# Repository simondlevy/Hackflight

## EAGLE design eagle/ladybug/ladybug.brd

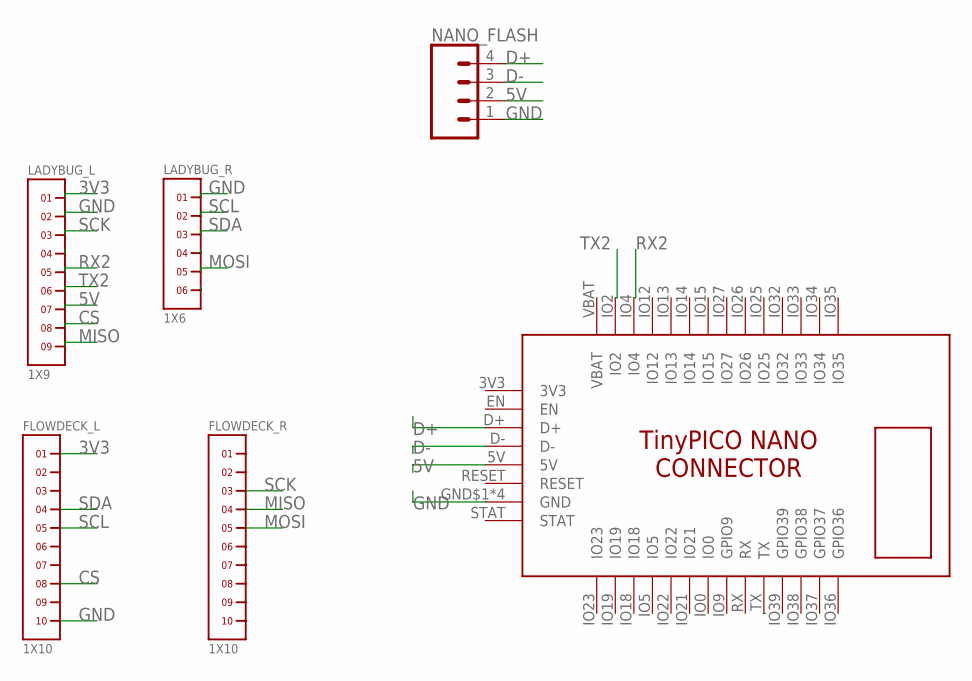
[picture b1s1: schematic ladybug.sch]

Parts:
FLOWDECK_L: 1X10
FLOWDECK_R: 1X10
LADYBUG_L: 1X9
LADYBUG_R: 1X6
NANO_FLASH: CONN_041X04_NO_SILK; 1X04_NO_SILK
U$1: TINYPICO-NANO-CONNECTOR

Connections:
3V3: FLOWDECK_L.1, LADYBUG_L.1, U$1.3V3
5V: LADYBUG_L.7, NANO_FLASH.2, U$1.5V
A0: LADYBUG_R.4
CS: FLOWDECK_L.8, LADYBUG_L.8
D+: NANO_FLASH.4, U$1.D+
D-: NANO_FLASH.3, U$1.D-
GND: FLOWDECK_L.10, LADYBUG_L.2, LADYBUG_R.1, NANO_FLASH.1, U$1.GND$1 (GND), U$1.GND$2 (GND), U$1.GND$3 (GND), U$1.GND$4 (GND)
LED: LADYBUG_L.4
MISO: FLOWDECK_R.4, LADYBUG_L.9
MOSI: FLOWDECK_R.5, LADYBUG_R.5
RX: U$1.TX
RX2: LADYBUG_L.5, U$1.IO4
SCK: FLOWDECK_R.3, LADYBUG_L.3
SCL: FLOWDECK_L.5, LADYBUG_R.2
SDA: FLOWDECK_L.4, LADYBUG_R.3
TX1: LADYBUG_R.6
TX2: LADYBUG_L.6, U$1.IO2
VBAT: U$1.VBAT

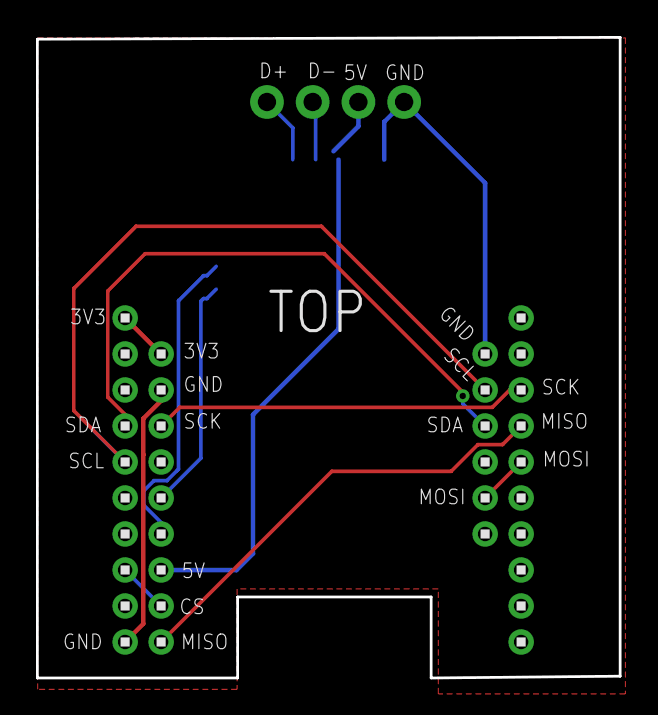
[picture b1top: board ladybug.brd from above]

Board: 2 copper layers, 32.4 x 35.6 mm, 6 parts (1 on the bottom side), 13 nets.

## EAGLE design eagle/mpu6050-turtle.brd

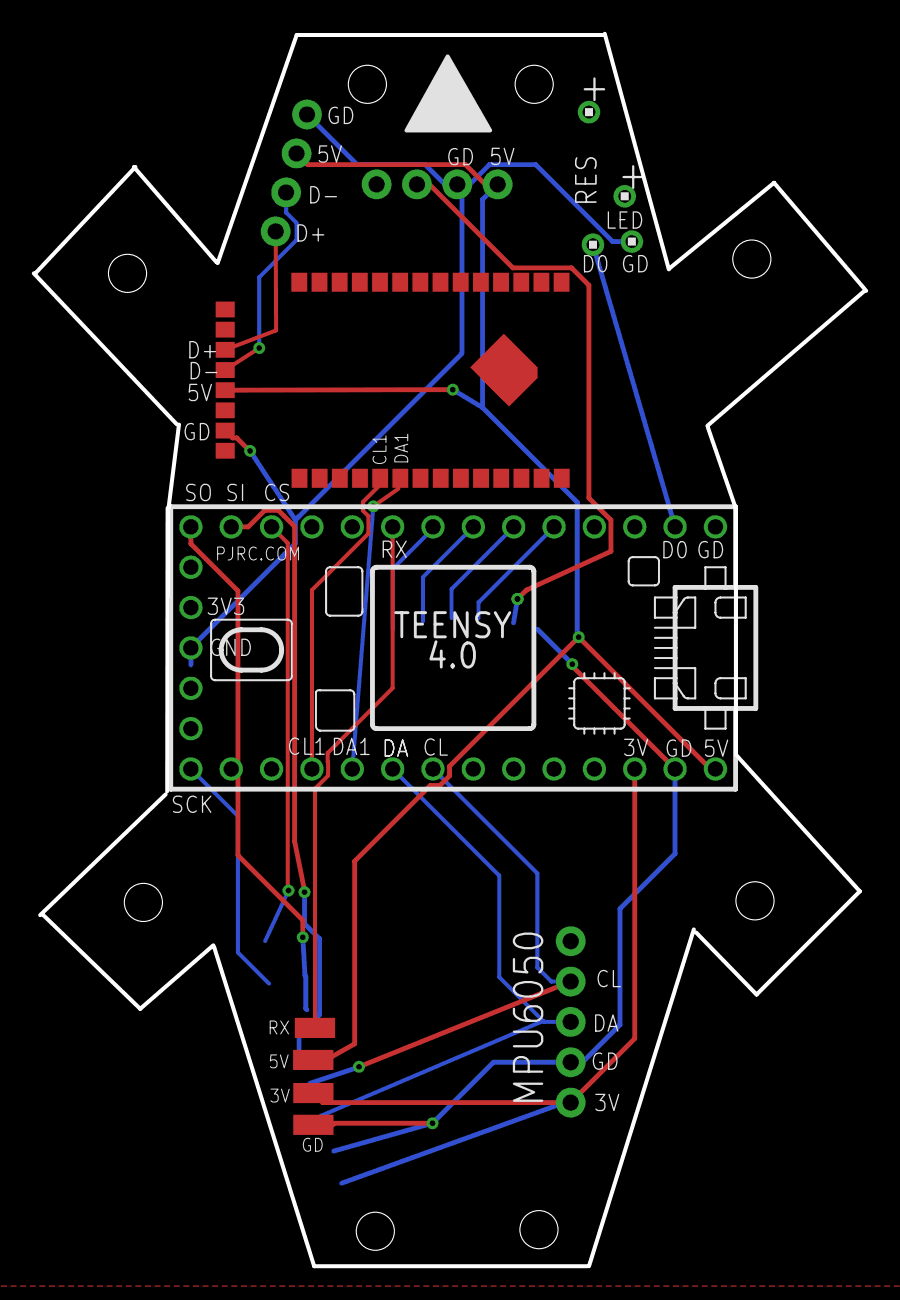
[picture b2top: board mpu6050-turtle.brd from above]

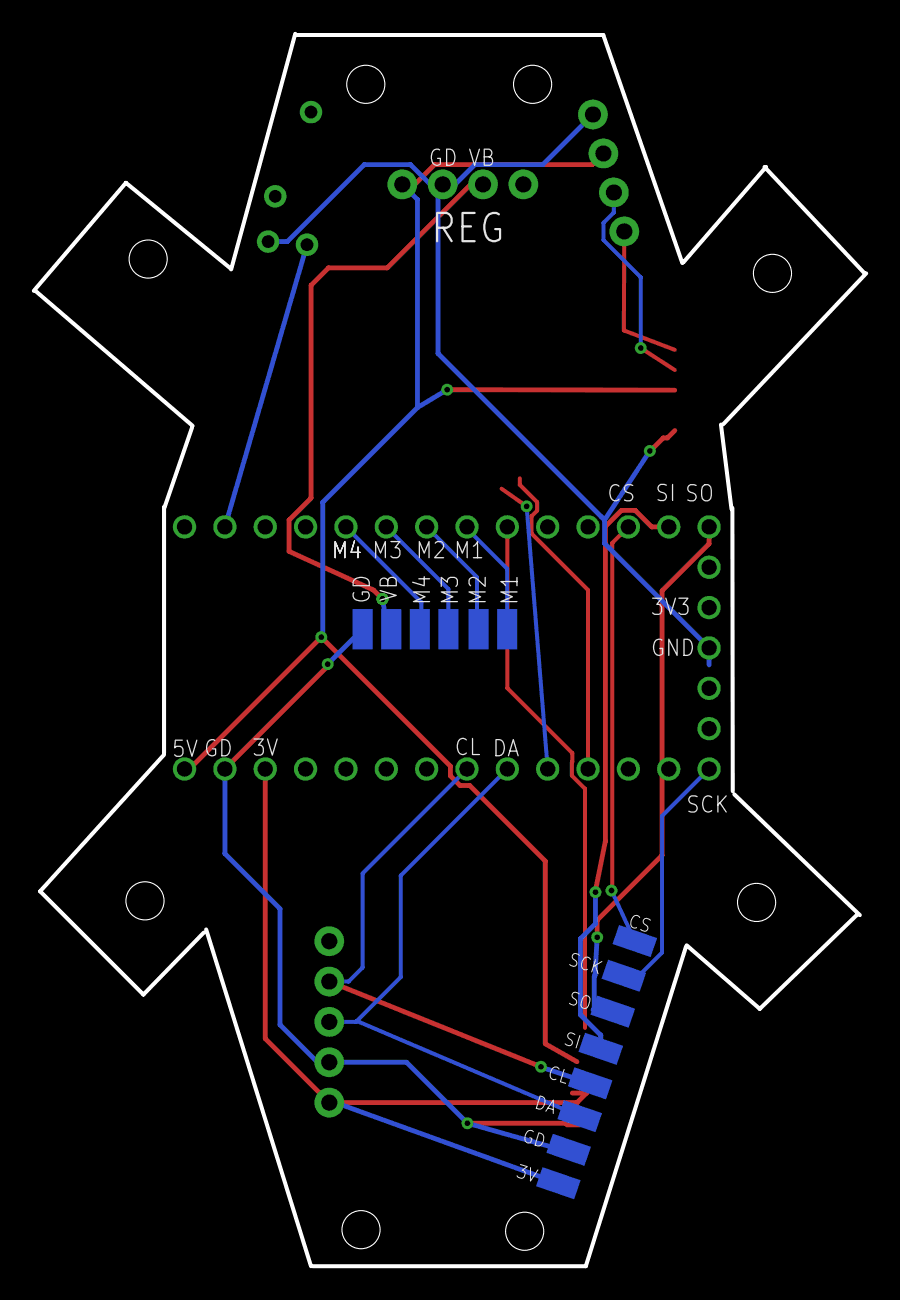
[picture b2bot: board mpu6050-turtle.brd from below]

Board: 2 copper layers, 52.4 x 77.6 mm, 27 parts (14 on the bottom side), 21 nets.

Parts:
3V, 3V1, 3V2, 3V3: SMD1,27-2,54
CS: SMD1,27-2,54
GD, GD1, GD2: SMD1,27-2,54
GND: SMD1,27-2,54
J1: 1X05_NO_SILK
J2: 1X04_NO_SILK
M1, M2, M3, M4: SMD1,27-2,54
REG: 1X04_NO_SILK
RX, RX1, RX2: SMD1,27-2,54
SCK: SMD1,27-2,54
U$1: TEENSY_4.0
U$2: TINYPICO-NANO-CONNECTOR
U$3, U$4, U$6, U$7: 1X1
VBAT: SMD1,27-2,54

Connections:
3V3: 3V.1, 3V2.1, J1.1, U$1.3V3_LO, U$2.3V3
5V: 3V1.1, J2.2, REG.1, U$1.VIN, U$2.5V
CS: CS.1, U$1.10/CS
D+: J2.4, U$2.D+
D-: J2.3, U$2.D-
GND: GD.1, GD1.1, GND.1, J1.2, J2.1, REG.2, U$1.GND2, U$1.GND3, U$2.GND$1, U$2.GND$2, U$2.GND$3, U$2.GND$4, U$7.1
LED_R_IN: U$1.0/RX, U$3.1
LED_R_OUT: U$4.1, U$6.1
M1: M1.1, U$1.6
M2: M2.1, U$1.5
M3: M3.1, U$1.4/CANRX
M4: M4.1, U$1.3/CANTX
MISO: 3V3.1, U$1.12/MISO
MOSI: RX2.1, U$1.11/MOSI
RX: RX.1, U$1.7
SCK: SCK.1, U$1.13/SCK
SCL: GD2.1, J1.4, U$1.19/A5/SCL
SCL1: U$1.16/A2, U$2.IO22
SDA: J1.3, RX1.1, U$1.18/A4/SDA
SDA1: U$1.17/A3, U$2.IO21
VB: REG.3, U$2.VBAT, VBAT.1

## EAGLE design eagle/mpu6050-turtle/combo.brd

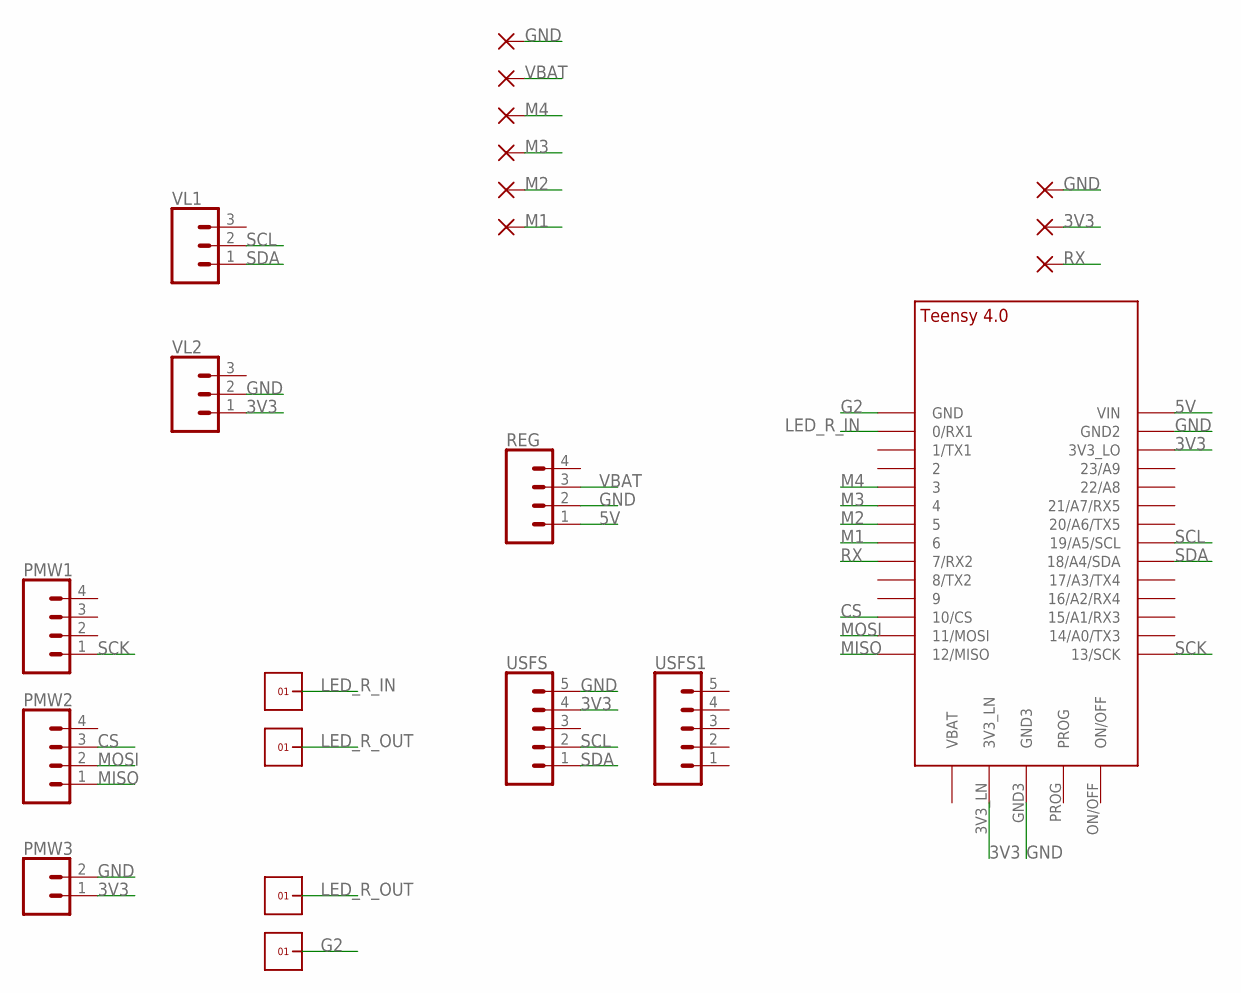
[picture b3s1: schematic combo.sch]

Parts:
3V: SMD2; SMD1,27-2,54
GD: SMD2; SMD1,27-2,54
GND: SMD2; SMD1,27-2,54
M1, M2, M3, M4: SMD2; SMD1,27-2,54
PMW1, PMW2: CONN_041X04_NO_SILK; 1X04_NO_SILK
PMW3: CONN_021X02_NO_SILK; 1X02_NO_SILK
REG: CONN_041X04_NO_SILK; 1X04_NO_SILK
RX: SMD2; SMD1,27-2,54
U$1: TEENSY_4.0
U$3, U$4, U$6, U$7: 1X1
USFS, USFS1: CONN_05NO_SILK; 1X05_NO_SILK
VBAT: SMD2; SMD1,27-2,54
VL1, VL2: CONN_031X03_NO_SILK; 1X03_NO_SILK

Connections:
3V3: 3V.1, PMW3.1, U$1.3V3_LN, U$1.3V3_LO, USFS.4, VL2.1; also elsewhere on the board
5V: REG.1, U$1.VIN
CS: PMW2.3, U$1.10/CS
G2: U$1.GND, U$7.1
GND: GD.1, GND.1, PMW3.2, REG.2, U$1.GND2, U$1.GND3, USFS.5, VL2.2; also elsewhere on the board
LED_R_IN: U$1.0/RX (0/RX1), U$3.1
LED_R_OUT: U$4.1, U$6.1
M1: M1.1, U$1.6
M2: M2.1, U$1.5
M3: M3.1, U$1.4/CANRX (4)
M4: M4.1, U$1.3/CANTX (3)
MISO: PMW2.1, U$1.12/MISO
MOSI: PMW2.2, U$1.11/MOSI
RX: RX.1, U$1.7 (7/RX2)
SCK: PMW1.1, U$1.13/SCK
SCL: U$1.19/A5/SCL, USFS.2, VL1.2; also elsewhere on the board
SDA: U$1.18/A4/SDA, USFS.1, VL1.1; also elsewhere on the board
VBAT: REG.3, VBAT.1

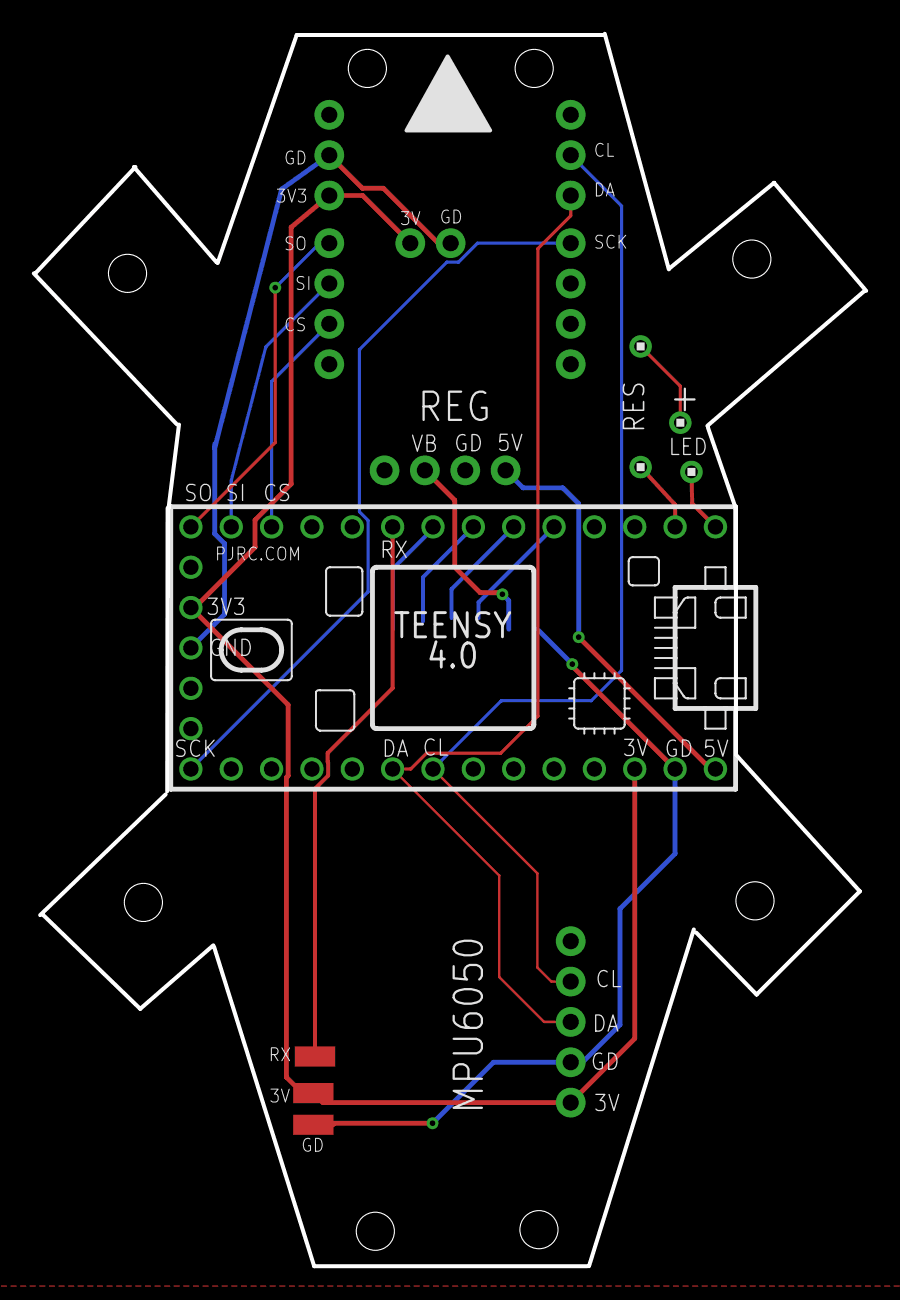
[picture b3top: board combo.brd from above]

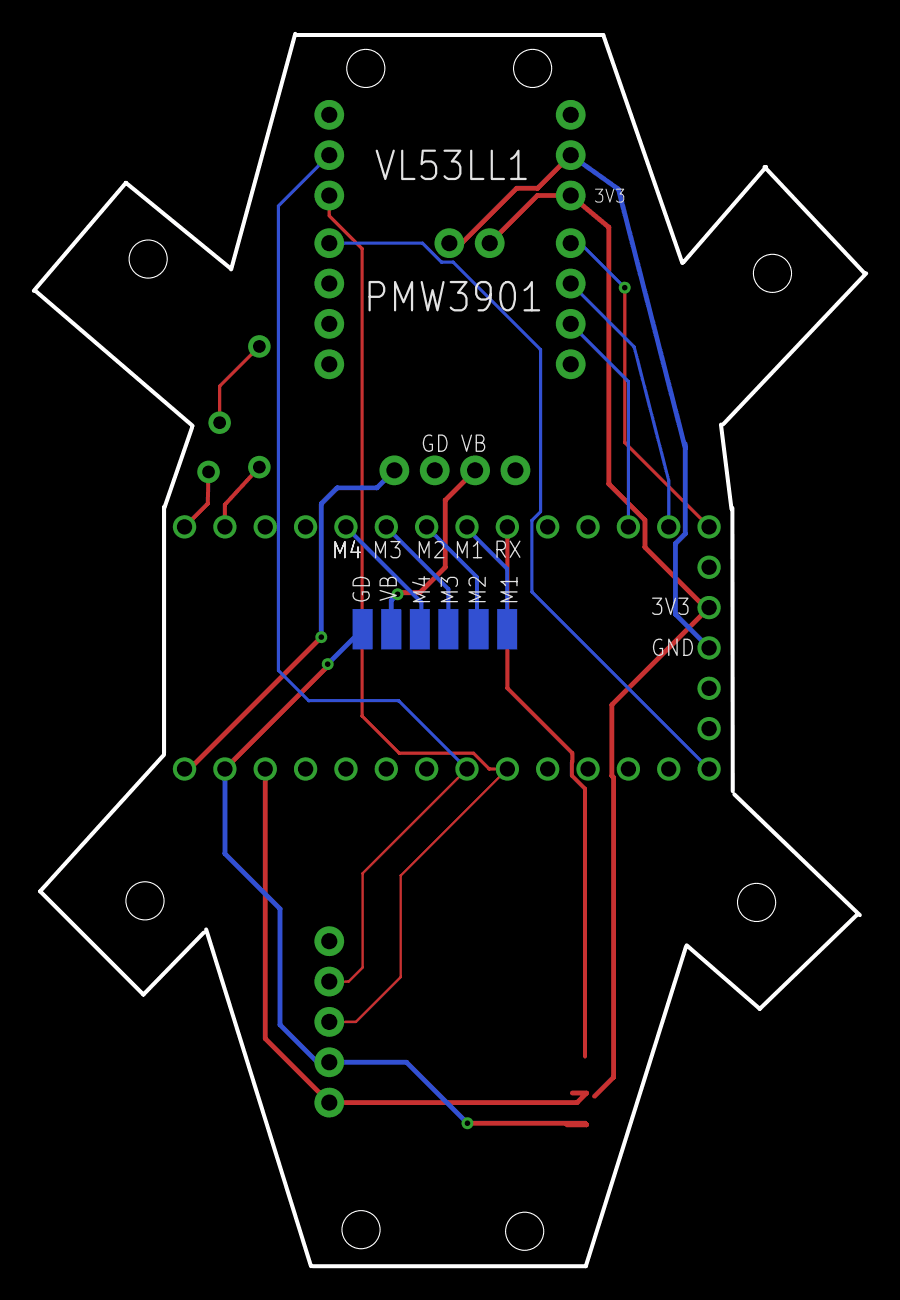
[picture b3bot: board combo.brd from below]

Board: 2 copper layers, 52.4 x 77.6 mm, 21 parts (6 on the bottom side), 18 nets.

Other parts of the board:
J1: 1X05_NO_SILK

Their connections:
3V3: J1.1; also elsewhere on the board
GND: J1.2; also elsewhere on the board
SCL: J1.4; also elsewhere on the board
SDA: J1.3; also elsewhere on the board

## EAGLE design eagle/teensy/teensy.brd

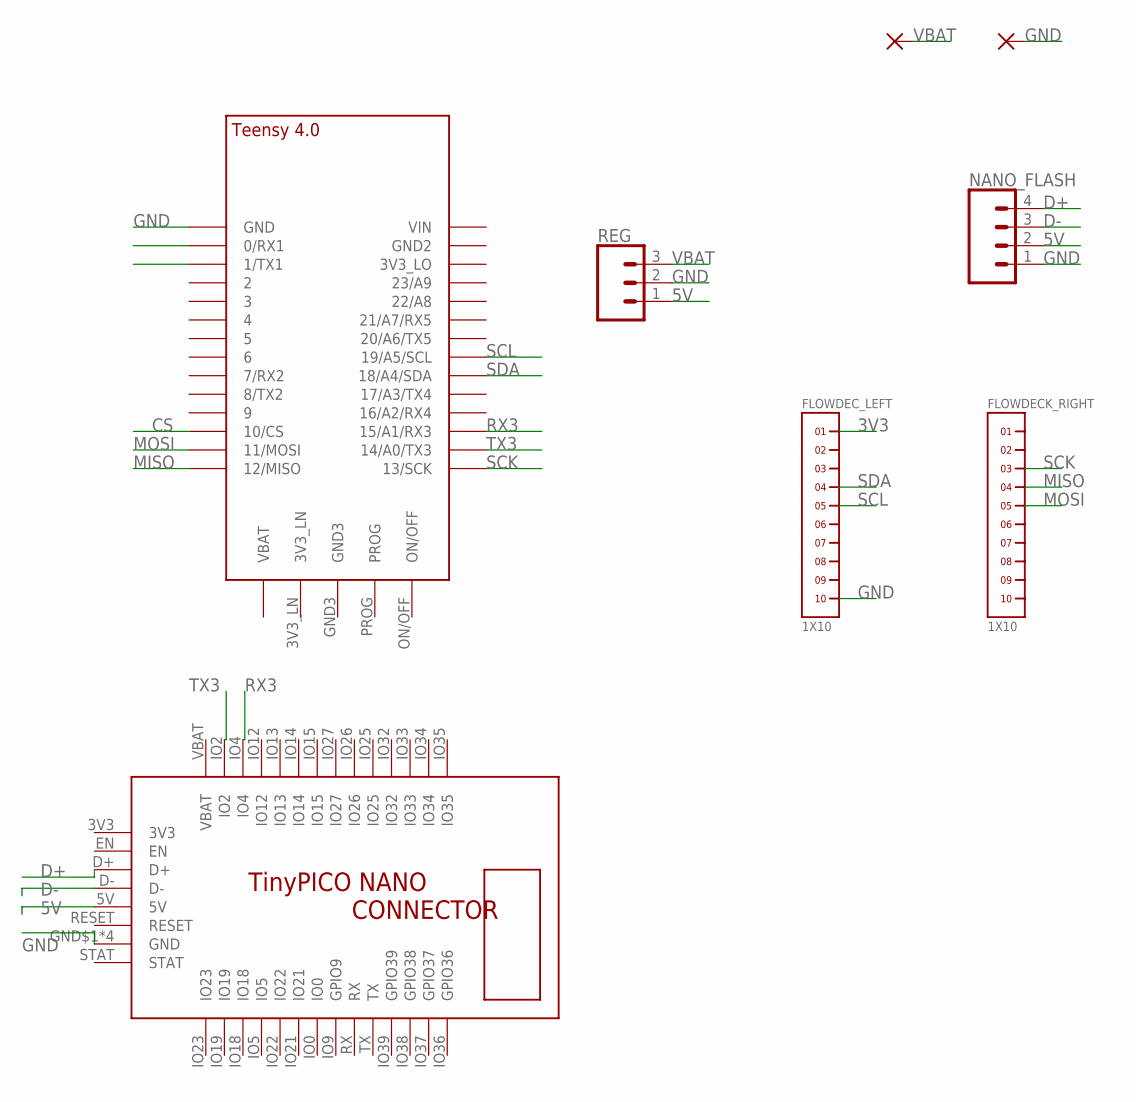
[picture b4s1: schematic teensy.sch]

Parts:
FLOWDECK_RIGHT: 1X10
FLOWDEC_LEFT: 1X10
GND: SMD5; SMD2,54-5,08
NANO_FLASH: CONN_041X04_NO_SILK; 1X04_NO_SILK
REG: CONN_031X03_NO_SILK; 1X03_NO_SILK
U$1: TEENSY_4.0
U$2: TINYPICO-NANO-CONNECTOR
VBAT: SMD5; SMD2,54-5,08

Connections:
3V3: FLOWDEC_LEFT.1, U$2.3V3
5V: NANO_FLASH.2, REG.1, U$2.5V
CS: U$1.10/CS
D+: NANO_FLASH.4, U$2.D+
D-: NANO_FLASH.3, U$2.D-
GND: FLOWDEC_LEFT.10, GND.1, NANO_FLASH.1, REG.2, U$1.GND, U$2.GND$1 (GND), U$2.GND$2 (GND), U$2.GND$3 (GND), U$2.GND$4 (GND)
MISO: FLOWDECK_RIGHT.4, U$1.12/MISO
MOSI: FLOWDECK_RIGHT.5, U$1.11/MOSI
RX3: U$1.15/A1 (15/A1/RX3), U$2.IO4
SCK: FLOWDECK_RIGHT.3, U$1.13/SCK
SCL: FLOWDEC_LEFT.5, U$1.19/A5/SCL
SDA: FLOWDEC_LEFT.4, U$1.18/A4/SDA
TX3: U$1.14/A0 (14/A0/TX3), U$2.IO2
VBAT: REG.3, U$2.VBAT, VBAT.1

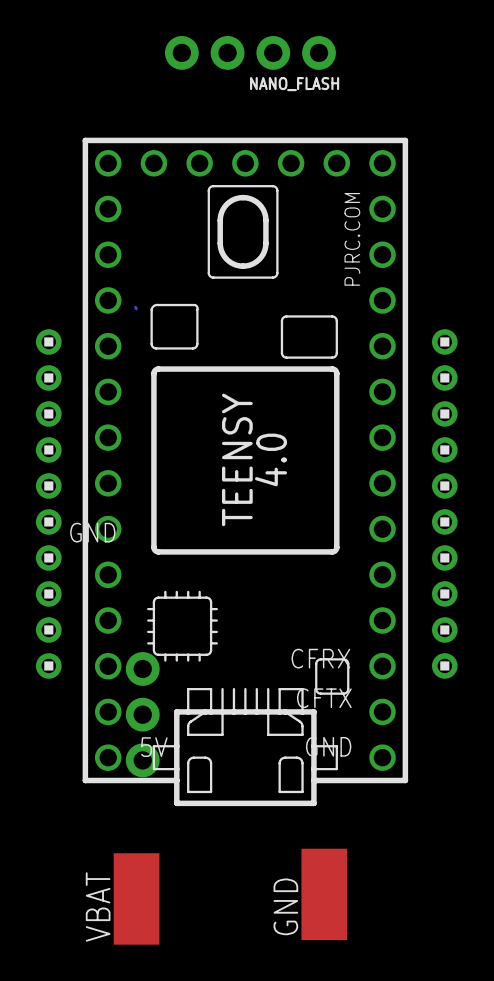
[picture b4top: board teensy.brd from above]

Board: 2 copper layers, 8 parts (1 on the bottom side), 13 nets.

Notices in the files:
parts and their libraries:
SparkFun-Connectors: Licensing: Creative Commons ShareAlike 4.0 International - https://creativecommons.org/licenses/by-sa/4.0
